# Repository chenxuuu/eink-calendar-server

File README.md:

# eink-calendar-server

电子日历服务端

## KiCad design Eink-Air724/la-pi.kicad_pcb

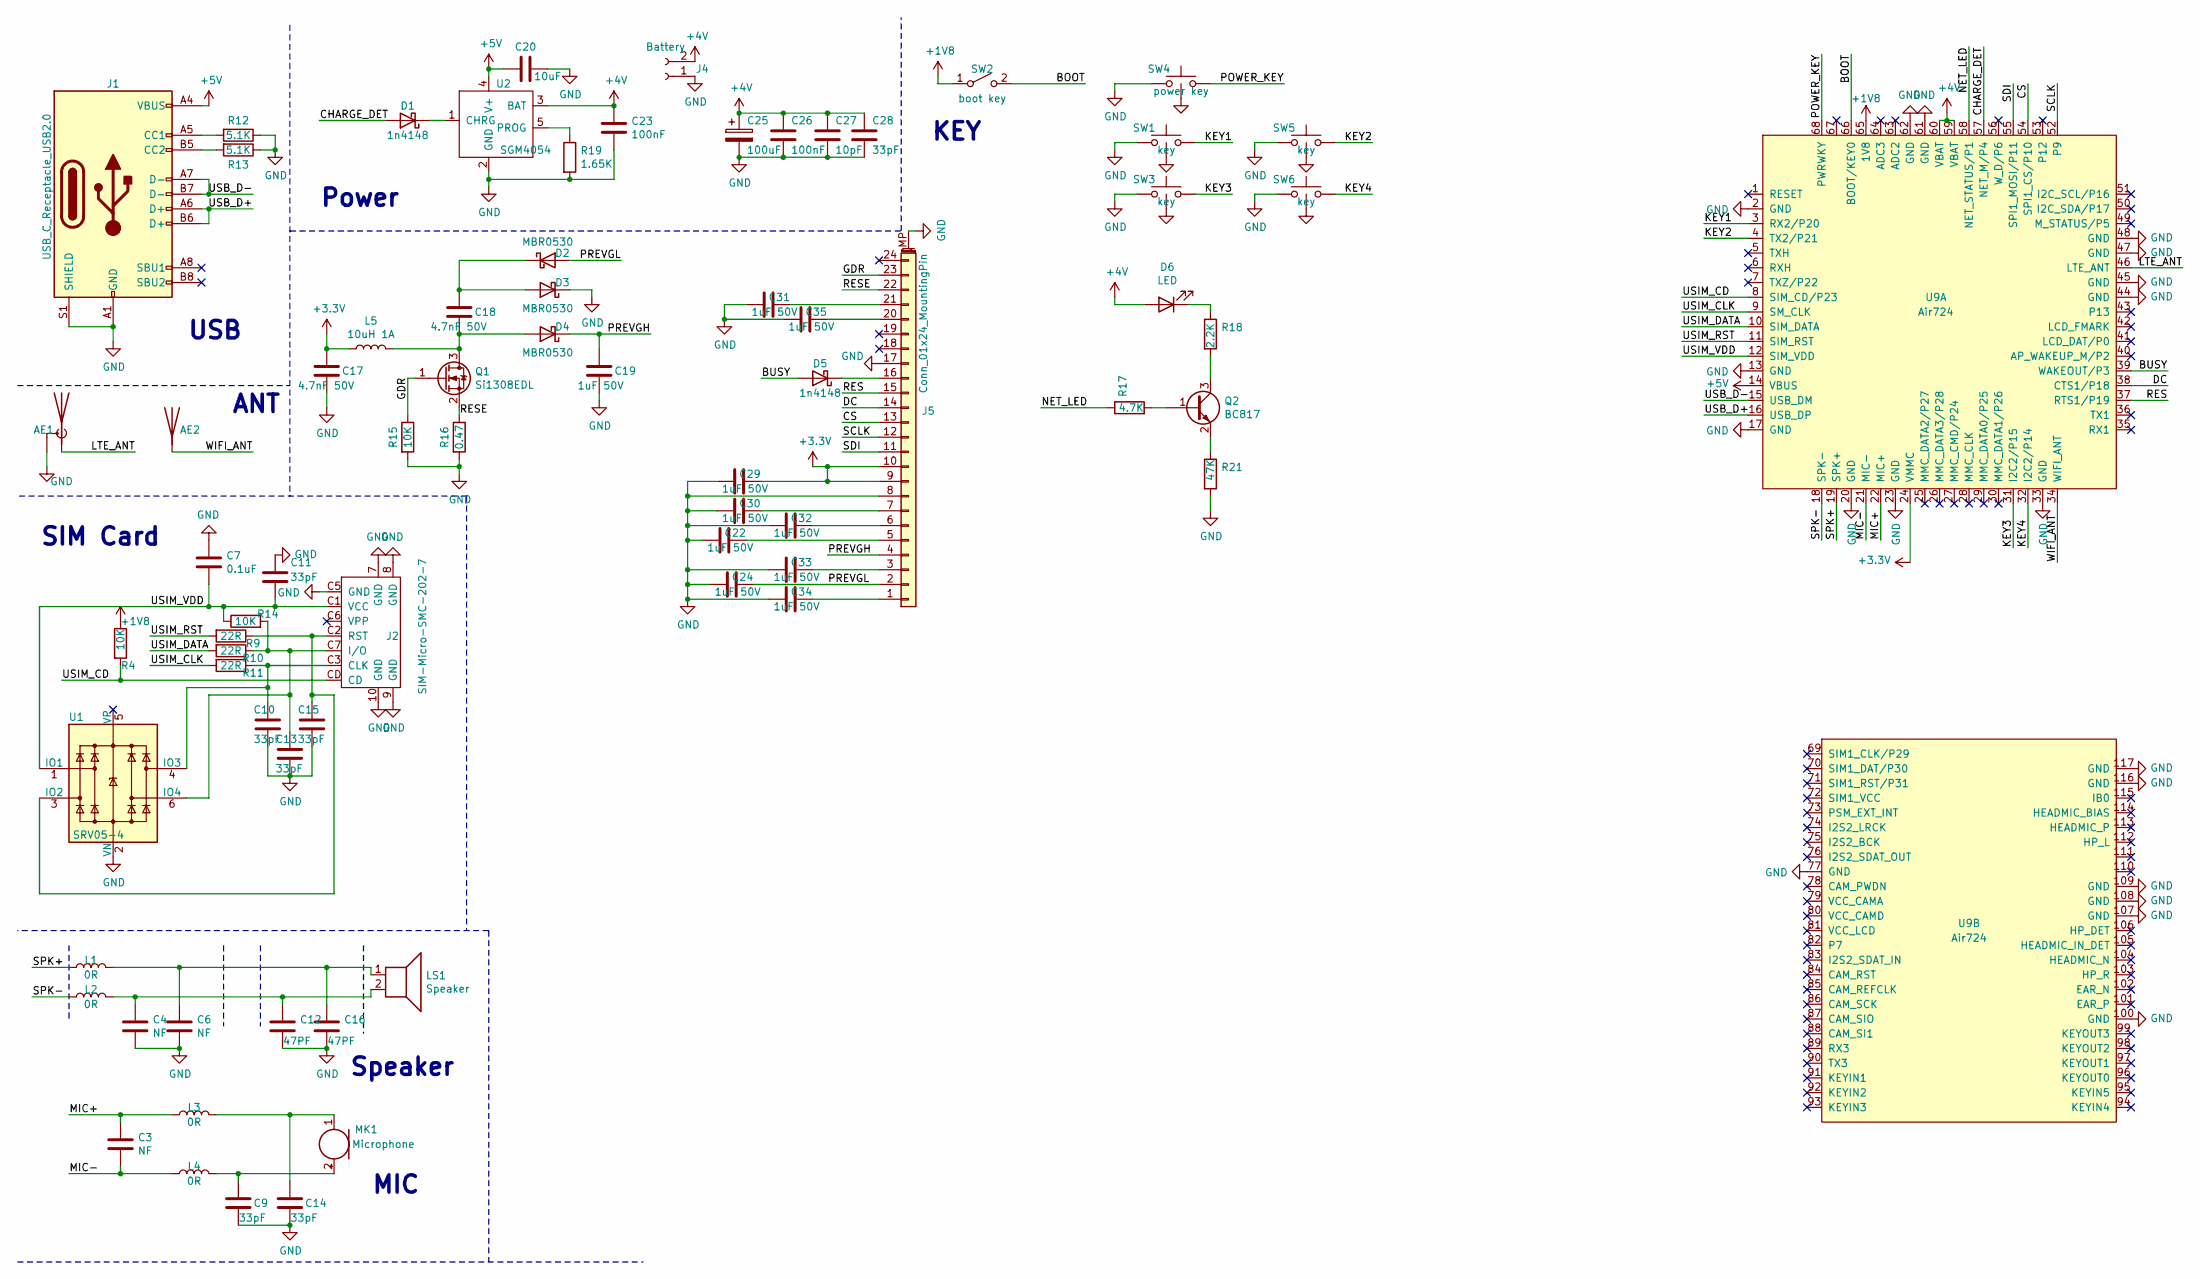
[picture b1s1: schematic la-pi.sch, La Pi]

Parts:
AE1: Antenna; IPEX
AE2: Antenna; Wifi_2.4GHz
C3, C4, C6: NF; C_0402_1005Metric
C7: 0.1uF; C_0402_1005Metric
C9, C10, C11, C13, C14, C15: 33pF; C_0402_1005Metric
C12, C16: 47PF; C_0402_1005Metric
C17, C18: 4.7nF 50V; C_0402_1005Metric
C19, C22, C24, C29, C30, C31, C32, C33, C34, C35: 1uF 50V; C_0402_1005Metric
C20: 10uF; C_0402_1005Metric
C23, C26: 100nF; C_0402_1005Metric
C25: 100uF; CP_EIA-1608-10_AVX-L_Pad1.25x1.05mm_HandSolder
C27: 10pF; C_0603_1608Metric
C28: 33pF; C_0603_1608Metric
D1, D5: 1n4148; D_SOD-323
D2, D3, D4: MBR0530; D_SOD-123
D6: LED; LED_0402_1005Metric
J1: USB_C_Receptacle_USB2.0; USB_C_Receptacle_HRO_TYPE-C-31-M-12
J2: SIM-Micro-SMC-202-7; SIM-SMD_SMC-202-7
J4: Battery; 2pin
J5: Conn_01x24_MountingPin; GDEW042T2
L1, L2, L3, L4: 0R; R_0402_1005Metric
L5: 10uH 1A; L_Bourns-SRN4018
LS1: Speaker; 2pin
MK1: Microphone; MIC-TH_BD4.0-P1.40-D0.4-L-FD
Q1: Si1308EDL; SOT-323_SC-70
Q2: BC817; SOT-23
R4, R14, R15: 10K; R_0402_1005Metric
R9, R10, R11: 22R; R_0402_1005Metric
R12, R13: 5.1K; R_0402_1005Metric
R16: 0.47; R_0402_1005Metric
R17: 4.7K; R_0402_1005Metric
R18: 2.2K; R_0402_1005Metric
R19: 1.65K; R_0402_1005Metric
R21: 47K; R_0402_1005Metric
SW1, SW3, SW5, SW6: key; KEY-01
SW2: boot key; 2pin
SW4: power key; KEY-01
U1: SRV05-4; SOT-23-6
U2: SGM4054; SOT-23-5
U9: Air724

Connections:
+1V8: R4.1, SW2.1 (A), U9.65 (1V8)
+3V3: C17.1, C29.2, J5.9, J5.10, L5.1, U9.24 (VMMC)
+4V: C23.1, C25.1, C26.1, C27.1, C28.1, D6.2 (A), J4.2, U2.3 (BAT), U9.59 (VBAT), U9.60 (VBAT)
+5V: C20.2, J1.A4 (VBUS), J1.A9 (VBUS), J1.B4 (VBUS), J1.B9 (VBUS), U2.4 (V+), U9.14 (VBUS)
/BOOT: SW2.2 (B), U9.66 (BOOT/KEY0)
/BUSY: D5.2 (A), U9.39 (WAKEOUT/P3)
/CHARGE_DET: D1.2 (A), U9.57 (NET_M/P4)
/CS: J5.13, U9.54 (SPI1_CS/P10)
/DC: J5.14, U9.38 (CTS1/P18)
/GDR: J5.23, Q1.1 (G), R15.1
/KEY1: SW1.2, U9.3 (RX2/P20)
/KEY2: SW5.2, U9.4 (TX2/P21)
/KEY3: SW3.2, U9.31 (I2C2/P15)
/KEY4: SW6.2, U9.32 (I2C2/P14)
/LTE_ANT: AE1.1 (A), U9.46 (LTE_ANT)
/MIC+: C3.1, L3.1, U9.22 (MIC+)
/MIC-: C3.2, L4.1, U9.21 (MIC-)
/NET_LED: R17.1, U9.58 (NET_STATUS/P1)
/POWER_KEY: SW4.2, U9.68 (PWRWKY)
/PREVGH: C19.1, D4.1 (K), J5.4
/PREVGL: C24.2, D2.2 (A), J5.2
/RES: J5.15, U9.37 (RTS1/P19)
/RESE: J5.22, Q1.2 (S), R16.1
/SCLK: J5.12, U9.52 (P9)
/SDI: J5.11, U9.55 (SPI1_MOSI/P11)
/SPK+: L1.1, U9.19 (SPK+)
/SPK-: L2.1, U9.18 (SPK-)
/USB_D+: J1.A6 (D+), J1.B6 (D+), U9.16 (USB_DP)
/USB_D-: J1.A7 (D-), J1.B7 (D-), U9.15 (USB_DM)
/USIM_CD: J2.CD, R4.2, U9.8 (SIM_CD/P23)
/USIM_CLK: R11.2, U9.9 (SM_CLK)
/USIM_DATA: R10.2, U9.10 (SIM_DATA)
/USIM_RST: R9.2, U9.11 (SIM_RST)
/USIM_VDD: C7.2, C11.2, J2.C1 (VCC), R14.1, U1.1 (IO1), U9.12 (SIM_VDD)
/WIFI_ANT: AE2.1, U9.34 (WIFI_ANT)
GND: AE1.2 (Shield), C4.2, C6.2, C7.1, C9.2, C10.2, C11.1, C12.2, C13.2, C14.2, C15.2, C16.2, C17.2, C19.2, C20.1, C22.1, C23.2, C24.1, C25.2, C26.2, C27.2, C28.2, C29.1, C30.1, C31.1, C32.1, C33.1, C34.1, C35.1, D3.1 (K), J1.A1 (GND), J1.A12 (GND), J1.B1 (GND), J1.B12 (GND), J1.S1 (SHIELD), J2.7 (GND), J2.8 (GND), J2.9 (GND), J2.10 (GND), J2.C5 (GND), J4.1, J5.8, J5.17, J5.MP (MountPin), R12.1, R13.1, R15.2, R16.2, R19.2, R21.2, SW1.1, SW1.3 (GND), SW3.1, SW3.3 (GND), SW4.1, SW4.3 (GND), SW5.1, SW5.3 (GND), SW6.1, SW6.3 (GND), U1.2 (VN), U2.2 (GND), U9.2 (GND), U9.13 (GND), U9.17 (GND), U9.20 (GND), U9.23 (GND), U9.33 (GND), U9.44 (GND), U9.45 (GND), U9.47 (GND), U9.48 (GND), U9.61 (GND), U9.62 (GND), U9.77 (GND), U9.100 (GND), U9.107 (GND), U9.108 (GND), U9.109 (GND), U9.116 (GND), U9.117 (GND)
unnamed: C9.1, L4.2, MK1.2 (+)
unnamed: C10.1, J2.C3 (CLK), R11.1, U1.4 (IO3)
unnamed: C4.1, C12.1, L2.2, LS1.2
unnamed: C13.1, J2.C7 (I/O), R10.1, R14.2, U1.6 (IO4)
unnamed: C14.1, L3.2, MK1.1 (-)
unnamed: C15.1, J2.C2 (RST), R9.1, U1.3 (IO2)
unnamed: C6.1, C16.1, L1.2, LS1.1
unnamed: C18.1, D2.1 (K), D3.2 (A)
unnamed: C18.2, D4.2 (A), L5.2, Q1.3 (D)
unnamed: C22.2, J5.5
unnamed: C30.2, J5.7
unnamed: C31.2, J5.21
unnamed: C32.2, J5.6
unnamed: C33.2, J5.3
unnamed: C34.2, J5.1
unnamed: C35.2, J5.20
unnamed: D1.1 (K), U2.1 (CHRG)
unnamed: D5.1 (K), J5.16
unnamed: D6.1 (K), R18.1
unnamed: J1.A5 (CC1), R12.2
unnamed: J1.B5 (CC2), R13.2
unnamed: Q2.1 (B), R17.2
unnamed: Q2.2 (E), R21.1
unnamed: Q2.3 (C), R18.2
unnamed: R19.1, U2.5 (PROG)

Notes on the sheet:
USB
Power
ANT
SIM Card
Speaker
MIC
KEY

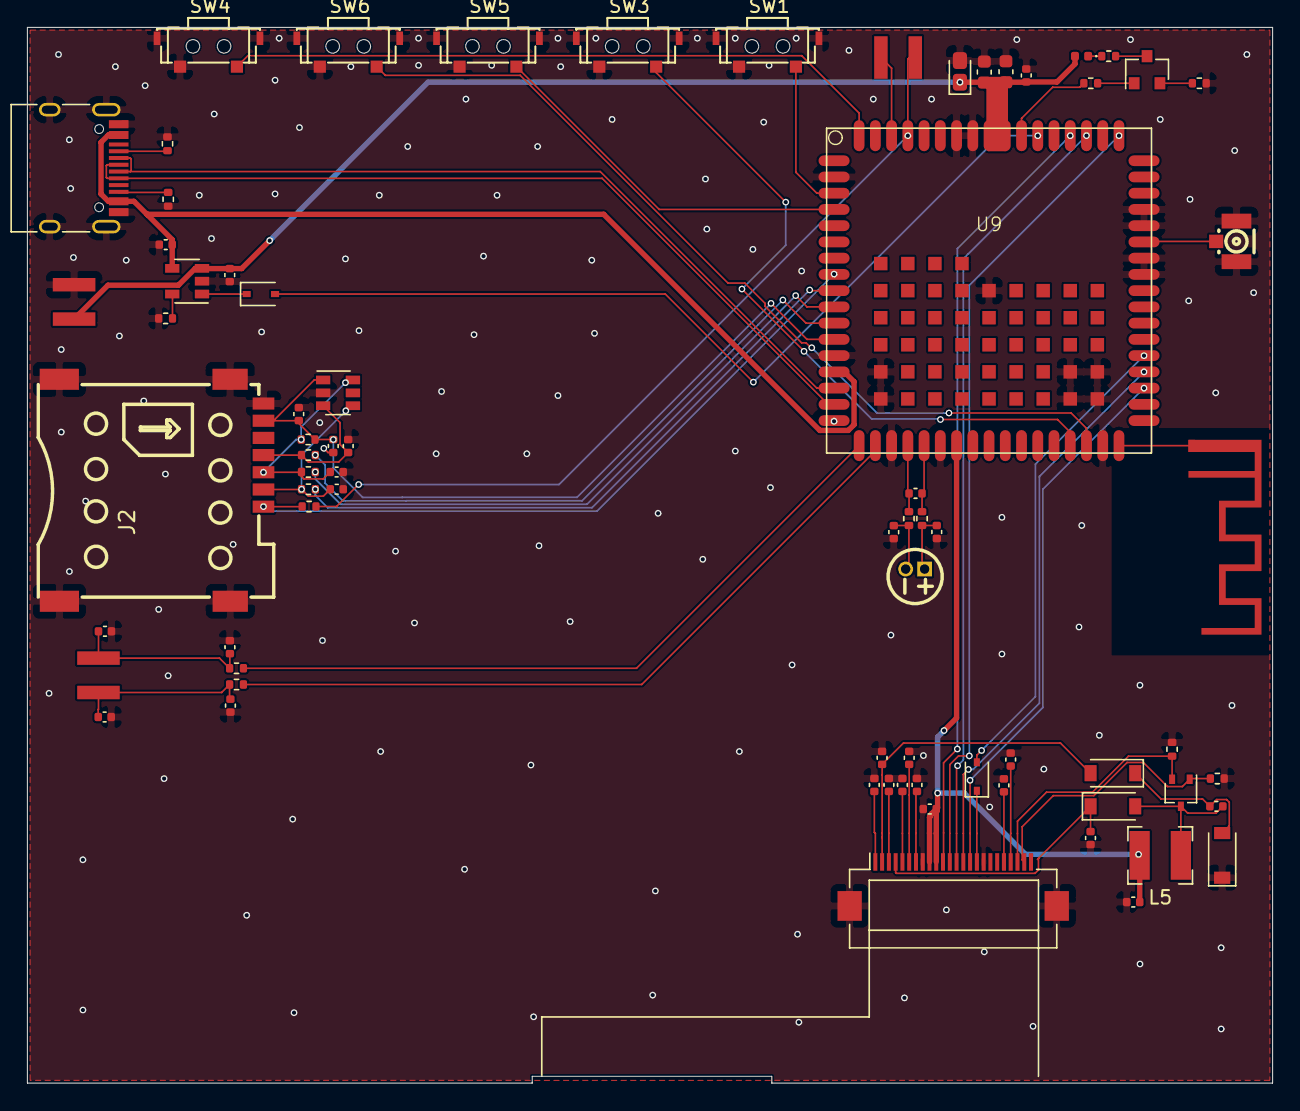
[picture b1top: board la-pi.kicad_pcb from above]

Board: 2 copper layers, 92.0 x 78.0 mm, 73 parts (1 on the bottom side), 61 nets.

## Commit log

2021-05-18 能跑起来了
2021-05-19 字体文件拎出来，用io加载，不编译进代码了，太慢了
2021-05-19 测试下webhook管不管用
2021-05-19 测试路由改下，继续试webhook
2021-05-19 更正数位序，多加点字，顺便再测试下webhook
2021-05-20 天气接口换成新的
2021-05-20 可以显示天气了
2021-05-20 日历功能好了
2021-05-20 加上一言的接口
2021-05-20 更正电量显示问题
2021-05-20 上传模块lua代码
2021-05-20 支持灰度或黑白设置
2021-05-21 微调下代码
2021-05-21 加上温度显示
2021-05-21 调整下位置
2021-05-21 刷新时间改成一天三次
2021-05-21 诗词分割两行居中处理
2021-05-24 加个开机画面
2021-05-24 刷屏有点问题，改下
2021-05-24 微调下电量
2021-05-24 🔋图案的头往上一个像素
2021-05-28 添加外壳文件
2021-06-07 八点前就不显示一言了，不然浪费电
2021-06-17 改回去。。
2021-06-27 当一言炸了的时候，显示默认文本
2021-07-06 加上自定义文本功能
2021-07-06 字多了改小字
2021-07-12 硬件工程
2021-12-09 fix: 更正找不到图标时报错的问题
2021-12-17 add: 补两张图片
